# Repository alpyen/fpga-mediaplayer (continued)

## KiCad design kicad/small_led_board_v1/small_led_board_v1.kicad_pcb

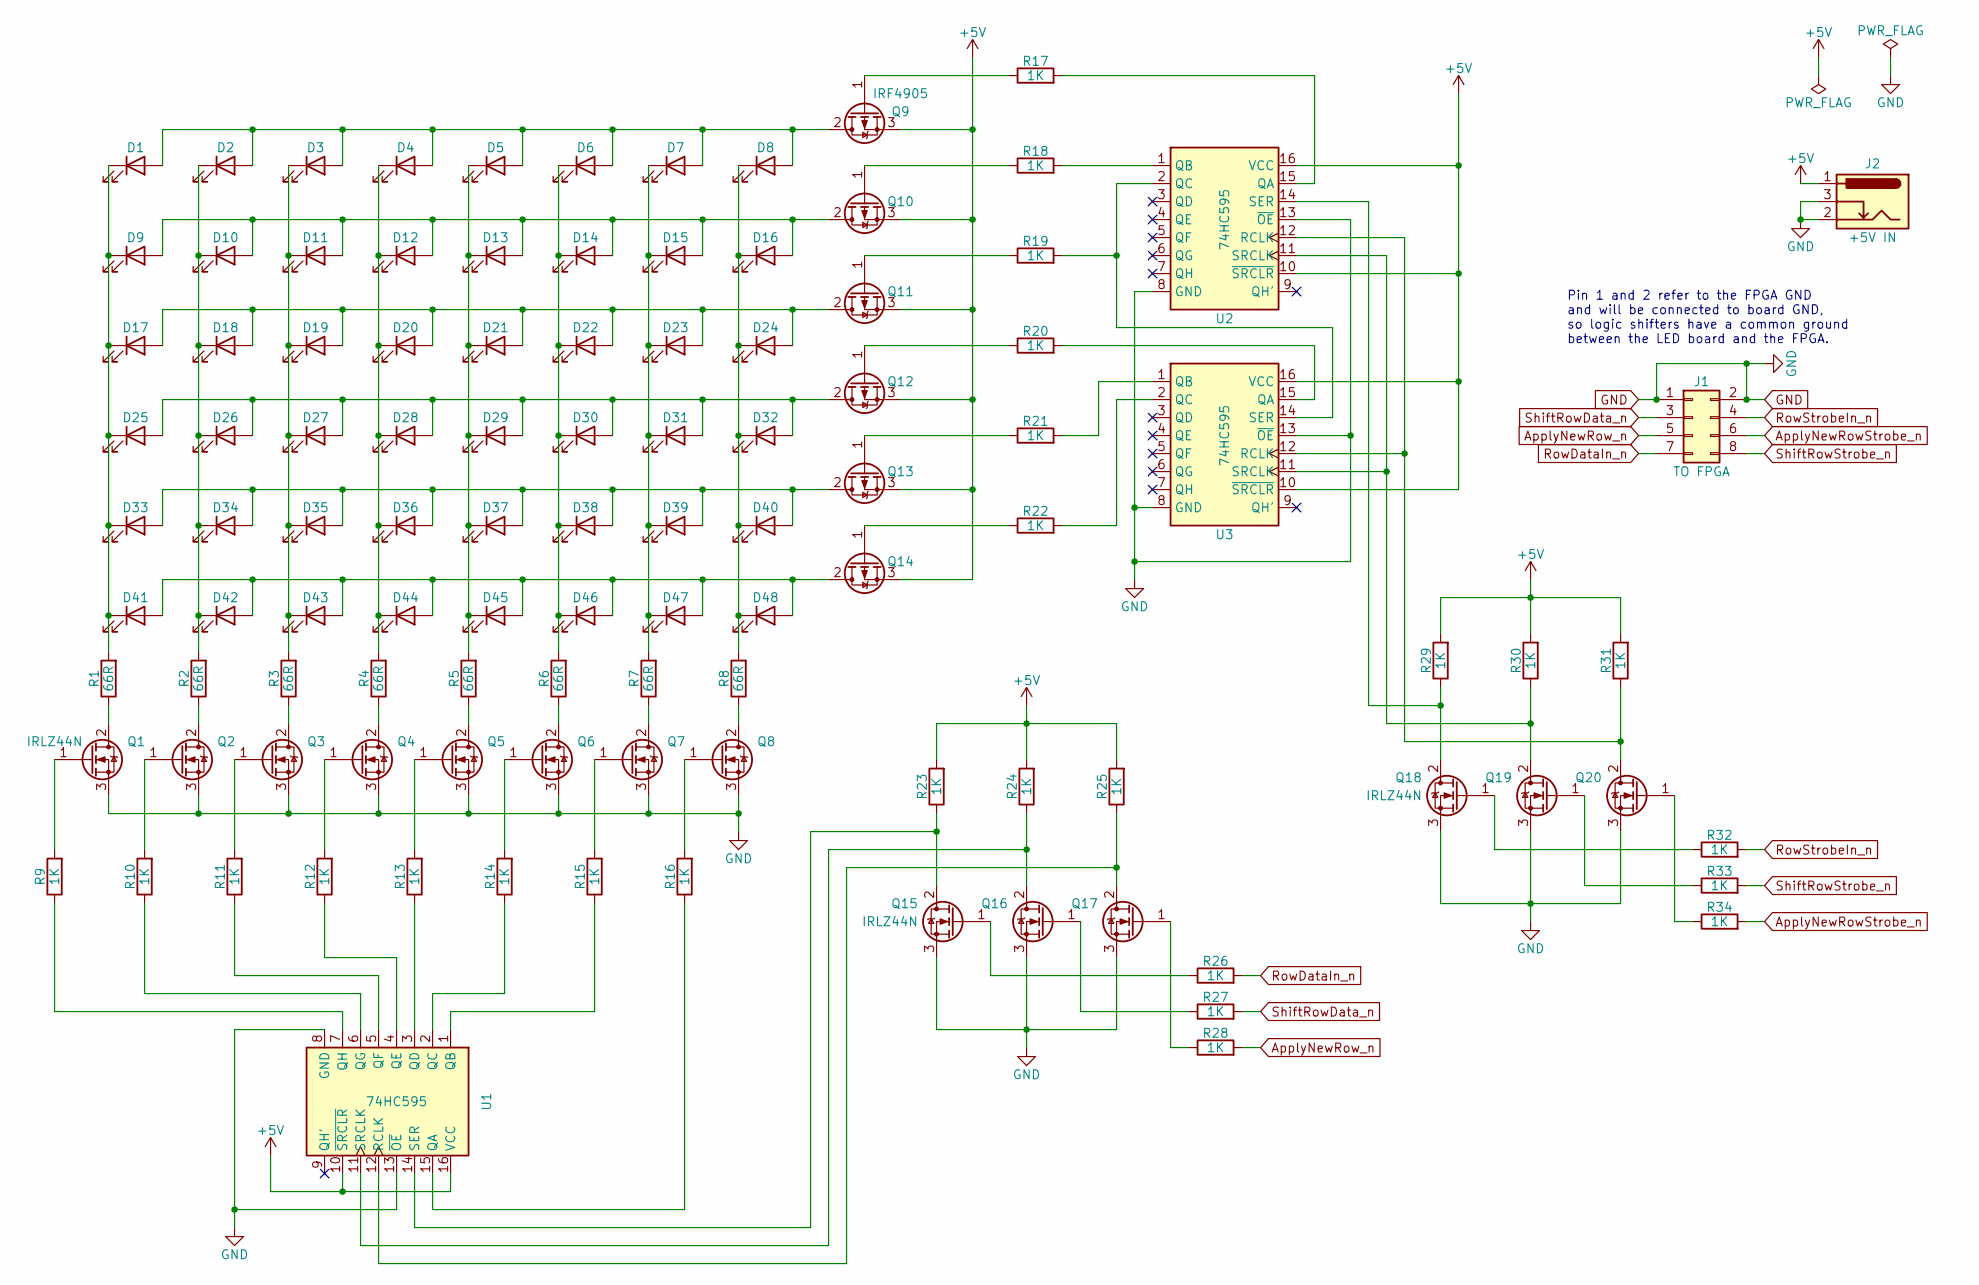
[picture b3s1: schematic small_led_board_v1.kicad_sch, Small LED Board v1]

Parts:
D1, D2, D3, D4, D5, D6, D7, D8, D9, D10, D11, D12, D13, D14, D15, D16, D17, D18, D19, D20, D21, D22, D23, D24, D25, D26, D27, D28, D29, D30, D31, D32, D33, D34, D35, D36, D37, D38, D39, D40, D41, D42, D43, D44, D45, D46, D47, D48: LED; LED_D5.0mm
J1: TO FPGA; PinSocket_2x04_P2.54mm_Horizontal
J2: +5V IN; BarrelJack_Horizontal
Q1, Q2, Q3, Q4, Q5, Q6, Q7, Q8, Q15, Q16, Q17, Q18, Q19, Q20: IRLZ44N; TO-220-3_Vertical
Q9, Q10, Q11, Q12, Q13, Q14: IRF4905; TO-220-3_Vertical
R1, R2, R3, R4, R5, R6, R7, R8: 66R; R_Axial_DIN0207_L6.3mm_D2.5mm_P7.62mm_Horizontal
R9, R10, R11, R12, R13, R14, R15, R16, R17, R18, R19, R20, R21, R22, R23, R24, R25, R26, R27, R28, R29, R30, R31, R32, R33, R34: 1K; R_Axial_DIN0207_L6.3mm_D2.5mm_P7.62mm_Horizontal
U1, U2, U3: 74HC595; DIP-16_W7.62mm

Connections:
+5V: J2.1, Q9.3 (S), Q10.3 (S), Q11.3 (S), Q12.3 (S), Q13.3 (S), Q14.3 (S), R23.2, R24.2, R25.2, R29.2, R30.2, R31.2, U1.10 (~SRCLR), U1.16 (VCC), U2.10 (~SRCLR), U2.16 (VCC), U3.10 (~SRCLR), U3.16 (VCC)
ApplyNewRowStrobe_n: J1.6, R34.2
ApplyNewRow_n: J1.5, R28.2
GND: J1.1, J1.2, J2.2, J2.3, Q1.3 (S), Q2.3 (S), Q3.3 (S), Q4.3 (S), Q5.3 (S), Q6.3 (S), Q7.3 (S), Q8.3 (S), Q15.3 (S), Q16.3 (S), Q17.3 (S), Q18.3 (S), Q19.3 (S), Q20.3 (S), U1.8 (GND), U1.13 (~OE), U2.8 (GND), U2.13 (~OE), U3.8 (GND), U3.13 (~OE)
unnamed: D1.2 (A), D2.2 (A), D3.2 (A), D4.2 (A), D5.2 (A), D6.2 (A), D7.2 (A), D8.2 (A), Q9.2 (D)
unnamed: D1.1 (K), D9.1 (K), D17.1 (K), D25.1 (K), D33.1 (K), D41.1 (K), R1.2
unnamed: D9.2 (A), D10.2 (A), D11.2 (A), D12.2 (A), D13.2 (A), D14.2 (A), D15.2 (A), D16.2 (A), Q10.2 (D)
unnamed: D2.1 (K), D10.1 (K), D18.1 (K), D26.1 (K), D34.1 (K), D42.1 (K), R2.2
unnamed: D3.1 (K), D11.1 (K), D19.1 (K), D27.1 (K), D35.1 (K), D43.1 (K), R3.2
unnamed: D4.1 (K), D12.1 (K), D20.1 (K), D28.1 (K), D36.1 (K), D44.1 (K), R4.2
unnamed: D5.1 (K), D13.1 (K), D21.1 (K), D29.1 (K), D37.1 (K), D45.1 (K), R5.2
unnamed: D6.1 (K), D14.1 (K), D22.1 (K), D30.1 (K), D38.1 (K), D46.1 (K), R6.2
unnamed: D7.1 (K), D15.1 (K), D23.1 (K), D31.1 (K), D39.1 (K), D47.1 (K), R7.2
unnamed: D8.1 (K), D16.1 (K), D24.1 (K), D32.1 (K), D40.1 (K), D48.1 (K), R8.2
unnamed: D17.2 (A), D18.2 (A), D19.2 (A), D20.2 (A), D21.2 (A), D22.2 (A), D23.2 (A), D24.2 (A), Q11.2 (D)
unnamed: D25.2 (A), D26.2 (A), D27.2 (A), D28.2 (A), D29.2 (A), D30.2 (A), D31.2 (A), D32.2 (A), Q12.2 (D)
unnamed: D33.2 (A), D34.2 (A), D35.2 (A), D36.2 (A), D37.2 (A), D38.2 (A), D39.2 (A), D40.2 (A), Q13.2 (D)
unnamed: D41.2 (A), D42.2 (A), D43.2 (A), D44.2 (A), D45.2 (A), D46.2 (A), D47.2 (A), D48.2 (A), Q14.2 (D)
unnamed: Q1.2 (D), R1.1
unnamed: Q1.1 (G), R9.2
unnamed: Q2.2 (D), R2.1
unnamed: Q2.1 (G), R10.2
unnamed: Q3.2 (D), R3.1
unnamed: Q3.1 (G), R11.2
unnamed: Q4.2 (D), R4.1
unnamed: Q4.1 (G), R12.2
unnamed: Q5.2 (D), R5.1
unnamed: Q5.1 (G), R13.2
unnamed: Q6.2 (D), R6.1
unnamed: Q6.1 (G), R14.2
unnamed: Q7.2 (D), R7.1
unnamed: Q7.1 (G), R15.2
unnamed: Q8.2 (D), R8.1
unnamed: Q8.1 (G), R16.2
unnamed: Q9.1 (G), R17.1
unnamed: Q10.1 (G), R18.1
unnamed: Q11.1 (G), R19.1
unnamed: Q12.1 (G), R20.1
unnamed: Q13.1 (G), R21.1
unnamed: Q14.1 (G), R22.1
unnamed: Q15.2 (D), R23.1, U1.14 (SER)
unnamed: Q15.1 (G), R26.1
unnamed: Q16.2 (D), R24.1, U1.11 (SRCLK)
unnamed: Q16.1 (G), R27.1
unnamed: Q17.2 (D), R25.1, U1.12 (RCLK)
unnamed: Q17.1 (G), R28.1
unnamed: Q18.2 (D), R29.1, U2.14 (SER)
unnamed: Q18.1 (G), R32.1
unnamed: Q19.2 (D), R30.1, U2.11 (SRCLK), U3.11 (SRCLK)
unnamed: Q19.1 (G), R33.1
unnamed: Q20.2 (D), R31.1, U2.12 (RCLK), U3.12 (RCLK)
unnamed: Q20.1 (G), R34.1
unnamed: R16.1, U1.15 (QA)
unnamed: R15.1, U1.1 (QB)
unnamed: R14.1, U1.2 (QC)
unnamed: R13.1, U1.3 (QD)
unnamed: R12.1, U1.4 (QE)
unnamed: R11.1, U1.5 (QF)
unnamed: R10.1, U1.6 (QG)
unnamed: R9.1, U1.7 (QH)
unnamed: R17.2, U2.15 (QA)
unnamed: R18.2, U2.1 (QB)
unnamed: R19.2, U2.2 (QC), U3.14 (SER)
unnamed: R20.2, U3.15 (QA)
unnamed: R21.2, U3.1 (QB)
unnamed: R22.2, U3.2 (QC)
RowDataIn_n: J1.7, R26.2
RowStrobeIn_n: J1.4, R32.2
ShiftRowData_n: J1.3, R27.2
ShiftRowStrobe_n: J1.8, R33.2

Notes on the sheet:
Pin 1 and 2 refer to the FPGA GND and will be connected to board GND, so logic shifters have a common ground between the LED board and the FPGA.

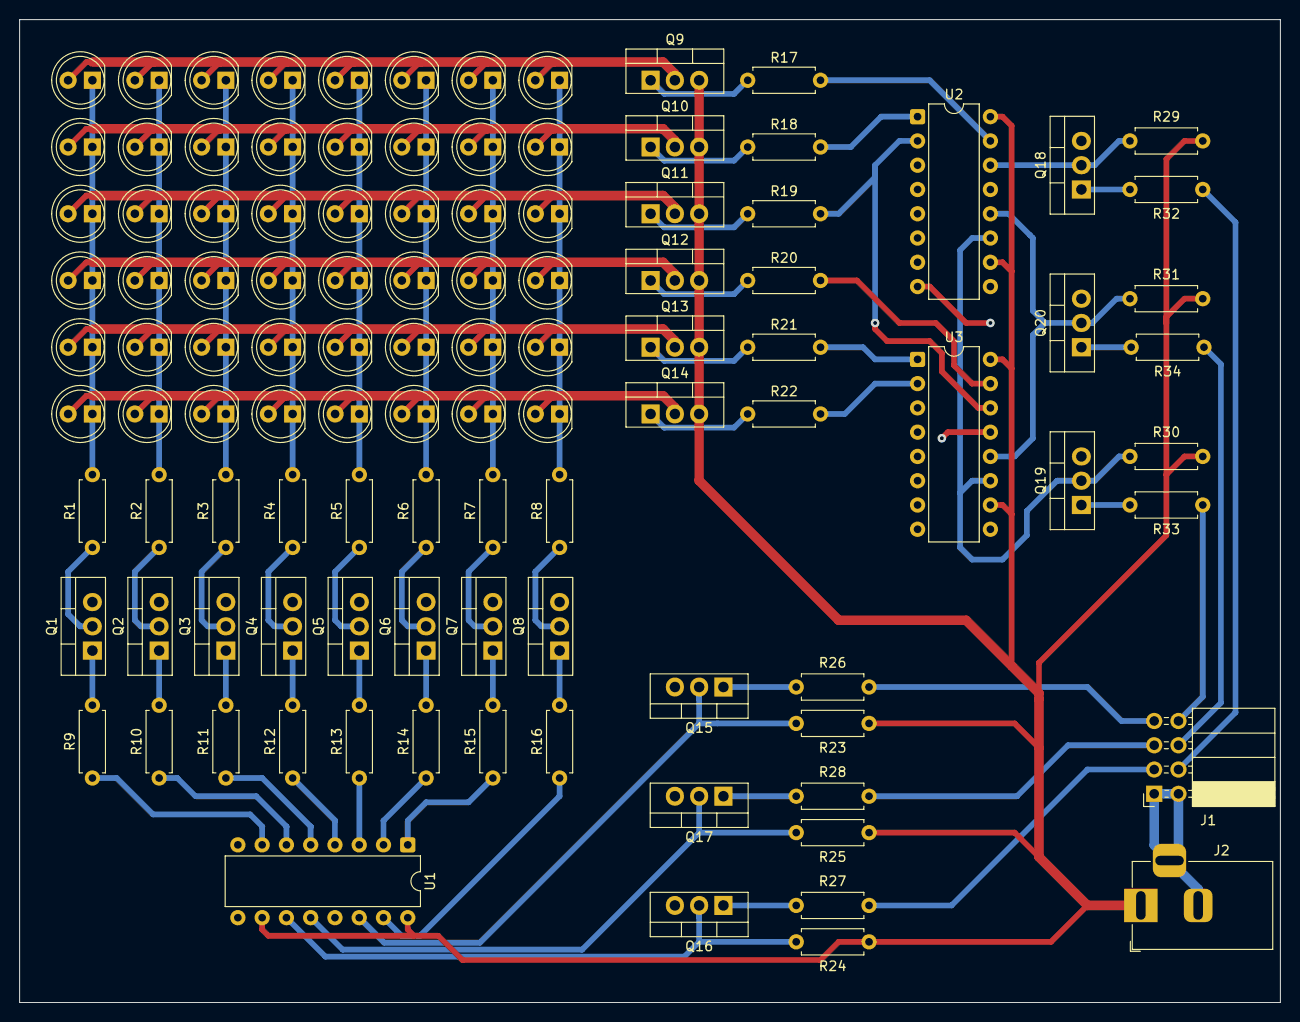
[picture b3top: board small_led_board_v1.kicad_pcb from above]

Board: 2 copper layers, 132.0 x 102.9 mm, 107 parts (0 on the bottom side), 70 nets.

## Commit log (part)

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2023-09-28 small_led_board: Update schematics
2023-09-28 small_led_board: Schematic updated, DRC pass
    - Schematic passes DRC check without any issue
    - LED resistors still need to be calculated after that the schematic should be finished
2023-09-29 small_led_board: PCB started
2023-10-02 small_led_board: Changed PCB settings
    Constraints were originally pulled from a git template project.
    Changed 4 layers to 2 layers as only Front and Back are needed.
2023-10-06 Update: Small board done
    The small board has been soldered and can be driven flawlessly from the digital pins of an Arduino.
2023-10-07 Set up base Vivado project with sim files
    Vivado project can be reconstructed by 'cd'-ing into the vivado/ subfolder and 'source'ing the tcl-script with tcl-console.
2023-10-11 sim: Exported simulation helper functions to own package
2023-10-12 Refactoring a bit
2023-10-13 Added how to open section to README.md
2023-10-14 hdl: Removed sim_pkg for now
2023-10-15 hdl: Fixed small_led_board testbench
2023-10-15 hdl: SPI Memory Driver implemented and tested
    Not certain if some signals need to be clocked or not.
    The simulation kinda differs from the real hardware so we'll implement a basic TLE to test it on the board.
2023-10-16 hdl: Added debouncer entity Writing a top-level-entity for board testing the spi memory driver.
2023-10-16 Updated gitignore to track IP xci-files
2023-10-18 hdl: Updated testbenches to fully test the flash
2023-10-18 hdl: Code cleanup
2023-11-21 hdl: renamed state enum
2023-11-21 README.md and added cc0 audio loop
2023-11-21 Update gitignore to ignore VSC workspace settings
2023-11-22 codec: Added progress information to script
2023-11-22 Refactor: WIP, Testbench
2023-11-22 sim: Done Refactoring!
2023-11-22 sim: Wired up forgotten SPI clock in testbench case
2023-11-23 sim: Fixed weird TB behaviour
    Will need further verification though to make sure it's not a delta race coincidence.
2023-11-23 hdl: Control Unit fills audio fifo
2023-11-24 hdl: Implementation of Control Unit mostly done
    All that's left to do is to add the video interface to it, right now there are stub signals.
2023-11-25 Refactored Code to eliminate trailing whitespaces
2023-11-25 hdl: Audio Driver started
2023-11-26 Audio Driver: Started, comb. loop needs fixing
    decoding_start and decoding_done are interfering with one another
2023-11-28 Control Unit: Added bit reversing for Fifo Data In
2023-12-01 I2S Master: CDC protocol written down
2023-12-03 I2S Master: Transfer FSM implemented
2023-12-05 I2S Master: sdata fixed
    The internal SCLK is 32*Fs but sdata was toggling every MCLK instead.
2023-12-05 XDC: Disabled timing between separate clocks and updated project file
    Fixed the reset of the i2s_master's new sample fifo. It used to unsynchronized signal.
2024-01-14 misc: updated readme and .gitignore
2024-01-16 videocodec/refactoring: started
2024-01-16 codec: added handling of empty streams
2024-01-18 refactor: renamed dump files
2024-01-20 player: added player to playback encoded video
2024-01-25 player: increased accuracy of fps calculation
2024-03-07 hdl: fixed signal semantics and added replay after playback is done
2024-03-09 media: added sample 8x6 encoded file
    the scripts are still hardcoded to 32x24, maybe that will change in the future, for now one 8x6 file should suffice for testing
2024-03-10 control unit: refactored fsm to be more concise
2024-03-11 frame buffer: implemented frame buffer memory
2024-03-20 video driver: added frame buffer
2024-06-05 clock calculator: jitter constraining added
2024-06-05 clock calculator: refactored
    Now on to implementing the max precision solutions for optimal skew and optimal sub clock deviation.
2024-06-07 video driver: phase accumulator implemented for video timing
2024-06-08 sim: changed out media file (8x6 resolution, half a second)
2024-06-12 frame buffer: added output registers
    This was an oversight, they were always meant to be registered. It came up when simulating the video driver.
2024-06-13 video driver: various fixes
    - Registered board_driver_frame_available, the logic for this is incomplete though. It has to be set in the decoder_fsm, and reset in the fsm. Remarked in notes.md
    - Moved selected_buffer toggle to different location.
    - Fixed the default value of new_pixel_value_next to be previous value so it survives state transitions.
2024-06-14 frame buffer: split data_a inout port to two separate ports
    - Changed the video driver alongside it
2024-06-18 video driver: fixed decoding for first frame
2024-06-19 codec/player: added command line argument for resolution
2024-06-19 video driver: fixed reading previous frame when reading first frame
    This way we don't have to reset the frame buffers back to zero before decoding video data. We had to do either of them otherwise it will corrupt the whole playback.
2024-06-19 misc: some notes added, cluttered readme, rewording comments
2024-06-19 docs: updated numbers for audio codec, cleaned readme
2024-06-20 docs: wrote readme for python scripts and added requirements
2024-06-27 readme: small led board will be revised
2024-06-28 readme: updated part selection
2024-07-01 small led board v2: schematics done for now
2024-07-03 small led board v2: fixed wrong connector schematic symbol
2024-07-03 small led board v2: routing done and plotted
    Also it was sent off to a manufacturer without major fixes. Just to see how it goes.
2024-07-06 small led board v2: added missing pull ups to schematic and pcb
    But the ordered PCB is obviously still missing those, they will be soldered on hacky on top just like it was meant to be.
2024-07-11 small led board v2: updated resistor values
2024-07-11 readme: v2 works on custom pcb
    This is a big success, the results are so good that we can simply develop the full size version without any restrictions. The board is able to clock it much faster than necessary.
    The only downside is that we are going to lose brightness. While we could compensate for that by reducing the 56 Ohm resistors to lower values, we want to stay in spec.
    Another approach would be to double the row data shift registers effectively duplicating brightness.
    This means that instead of 25% brightness, we would end up with 50%.
2024-07-12 fullsize led board: schematic for display
    This is still subject to change because I want the driver board to be as small as possible and the connecters have to be moved / changed.
2024-07-12 fullsize led board: display pcb wired
2024-07-14 fullsize led board: schematics for driver mostly done
    Removed also the bus stuff for the display and driver.
2024-07-14 fullsize led board: set pull up resistor values in schematic
    The 1M ohms was too low as I could pull the high-side switches' gates down with my body when touching those lines.
    100K was better as the transistor delivered less current but 10K managed to completely shut it off.
2024-07-15 fullsize led board: placed buffer and its pullups
2024-07-16 fullsize led board: rearranged high-side resistors to eliminate voltage divier
2024-07-16 fullsize led board: finished layouting and wiring the pcb
    Now to add some decoration and fix the LED resistor values.
2024-07-29 kicad: finalized led resistor values
2024-08-04 docs: corrected some old notes
2024-08-06 misc: it works but oops, i messed up the driver's pcb layout
    See notes.md on how and why.
    The new version of the board will have the row data shift registers wired up correctly.
2024-08-17 fullsize led board: fixed backwards wiring
    It's not as beautiful as I'd like to have it, but this will suffice, otherwise it will take way too much time to reroute the VIAs.
    If I want to improve this design further, I'd like to use SMD resistors anyway, so a full rerout would be necessary.
    Lesson learned I guess...
2024-08-19 vivado: activated assert checking for synthesis
2024-08-19 control unit: added resolution check
    This was open from the previous commit.
2024-08-19 docs: updated player section in python readme
    The player automatically decodes the resolution from the media file now.
2024-08-20 control unit: added generic to offset media file start in memory
2024-08-20 codec: improved encoding ratio and updated header
    - If no video was attached, the codec will write width=0 and height=0 into the header, so the control unit basically ignores this check.
    - The codec can now encode transitions beyond the bitdepth by wrapping them around. Since this is natural behaviour in hardware, this is a nice trick to squeeze a little bit more encoding ratio out.
    - Also added the option to exit the player by hitting the escape key.
    - Also updated the media files aswell.
2024-08-22 control unit: moved media base address from generic to port map
    This way, multiple files can be played back if appropriate hardware is wired onto this port.
2025-02-26 readme: restructured and added new points
2025-03-01 python: renamed scripts for upcoming refactoring
    - merger.py -> concat.py
    - header.py -> codec.py (moving en/decoding to here to debloat the other scripts)
2025-03-02 python: accelerated decoding and refactored player
    - codec.py now contains encoding and decoding routine.
    - player.py fully decodes before playback - no multiprocessing.
    - Multiprocessing the live decoding was scrapped because it was way too convoluted for the benefits. It introduced too much code to save 3 seconds startup time for large media files.
2025-03-02 player: added decoding hint and improved fps calculation accuracy
2025-03-02 player: added play/pause with space
2025-03-03 player: added mute by pressing 'm'
2025-03-04 docs: updated python readme, renamed files and deleted dumps
    - The dumps are not necessary anymore since the player can playback audio and video fast enough.
    - Renaming from .enc to .bin because it's easier to find the files in Vivado.
2025-03-08 docs: added section about combining bitfile and media for flash
2025-03-10 vivado: added basys3 board files
    Otherwise the project will not be regenerated correctly if somebody hasn't downloaded the Basys3 files from the Vivado store.
2025-04-12 board driver: reduced strobes per frame to 4 from 5
    Strobing it five times resulted in the last line flickering, most likely due to bad signal integrity.
    However four is still enough for the persistence of vision effect.
2025-04-14 board driver: fixed ghosting and last line staying on on last frame
2025-04-23 docs: refactored readme and updated media docs
2025-04-25 docs: vivado documentation complete
2025-04-26 kicad: migration complete to 9.0, small led boards both done
2025-04-27 docs: added documentation overview and minor changes
2025-04-29 docs: wip hdl, top level entity and memory driver done
2025-06-15 docs: updated player section with gif playback
2025-06-26 docs: wip kicad, fullsize board done, updated pictures and moved files
2025-07-18 readme: added youtube video
2025-07-20 docs: added light and dark mode variant of top level diagram
2025-08-04 fullsize led board: moved pullups to +3.3v of pmod
